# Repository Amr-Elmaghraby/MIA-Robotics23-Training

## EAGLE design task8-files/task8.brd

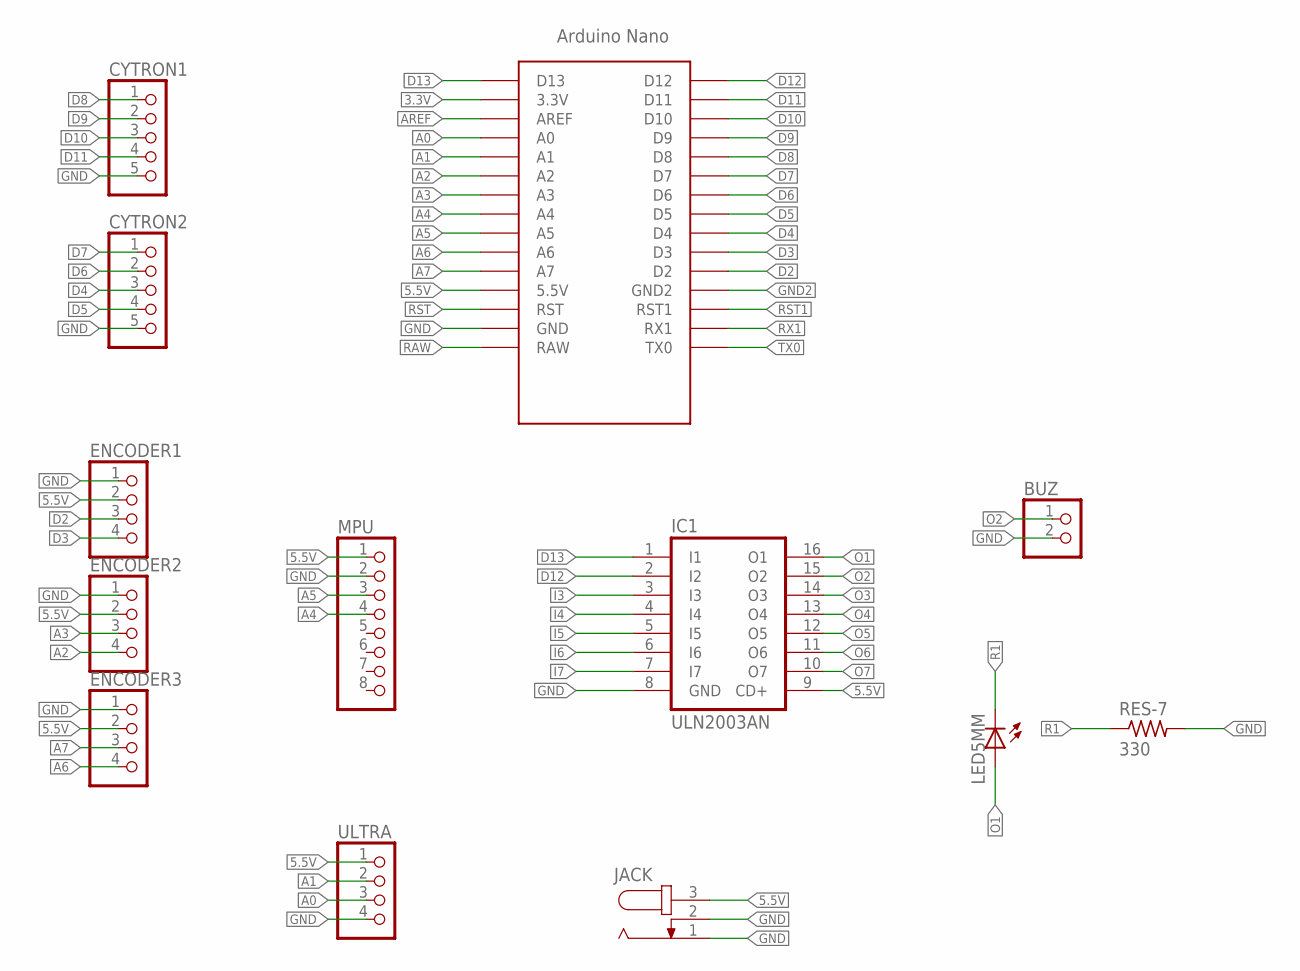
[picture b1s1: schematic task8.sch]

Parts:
330: RES-7; 0204/7
BUZ: PINHD-1X2; 1X02
CYTRON1, CYTRON2: PINHD-1X5; 1X05
ENCODER1, ENCODER2, ENCODER3: PINHD-1X4; 1X04
IC1: ULN2003AN; DIL16
JACK: JACK-PLUG0; SPC4077
MPU: PINHD-1X8; 1X08
U$1: ARDUINO_NANO; NANO
U$3: LED5MM
ULTRA: PINHD-1X4; 1X04

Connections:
3.3V: U$1.3.3V
5.5V: ENCODER1.2, ENCODER2.2, ENCODER3.2, IC1.9 (CD+), JACK.3, MPU.1, U$1.5V (5.5V), ULTRA.1
A0: U$1.A0, ULTRA.3
A1: U$1.A1, ULTRA.2
A2: ENCODER2.4, U$1.A2
A3: ENCODER2.3, U$1.A3
A4: MPU.4, U$1.A4
A5: MPU.3, U$1.A5
A6: ENCODER3.4, U$1.A6
A7: ENCODER3.3, U$1.A7
AREF: U$1.AREF
D2: ENCODER1.3, U$1.D2
D3: ENCODER1.4, U$1.D3
D4: CYTRON2.3, U$1.D4
D5: CYTRON2.4, U$1.D5
D6: CYTRON2.2, U$1.D6
D7: CYTRON2.1, U$1.D7
D8: CYTRON1.1, U$1.D8
D9: CYTRON1.2, U$1.D9
D10: CYTRON1.3, U$1.D10
D11: CYTRON1.4, U$1.D11
D12: IC1.2 (I2), U$1.D12
D13: IC1.1 (I1), U$1.D13
GND: 330.2, BUZ.2, CYTRON1.5, CYTRON2.5, ENCODER1.1, ENCODER2.1, ENCODER3.1, IC1.8 (GND), JACK.1, JACK.2, MPU.2, U$1.GND, ULTRA.4
GND2: U$1.GND1 (GND2)
I3: IC1.3 (I3)
I4: IC1.4 (I4)
I5: IC1.5 (I5)
I6: IC1.6 (I6)
I7: IC1.7 (I7)
O1: IC1.16 (O1), U$3.A
O2: BUZ.1, IC1.15 (O2)
O3: IC1.14 (O3)
O4: IC1.13 (O4)
O5: IC1.12 (O5)
O6: IC1.11 (O6)
O7: IC1.10 (O7)
R1: 330.1, U$3.K (C)
RAW: U$1.RAW
RST: U$1.RST
RST1: U$1.RST1
RX1: U$1.RX1
TX0: U$1.TX0

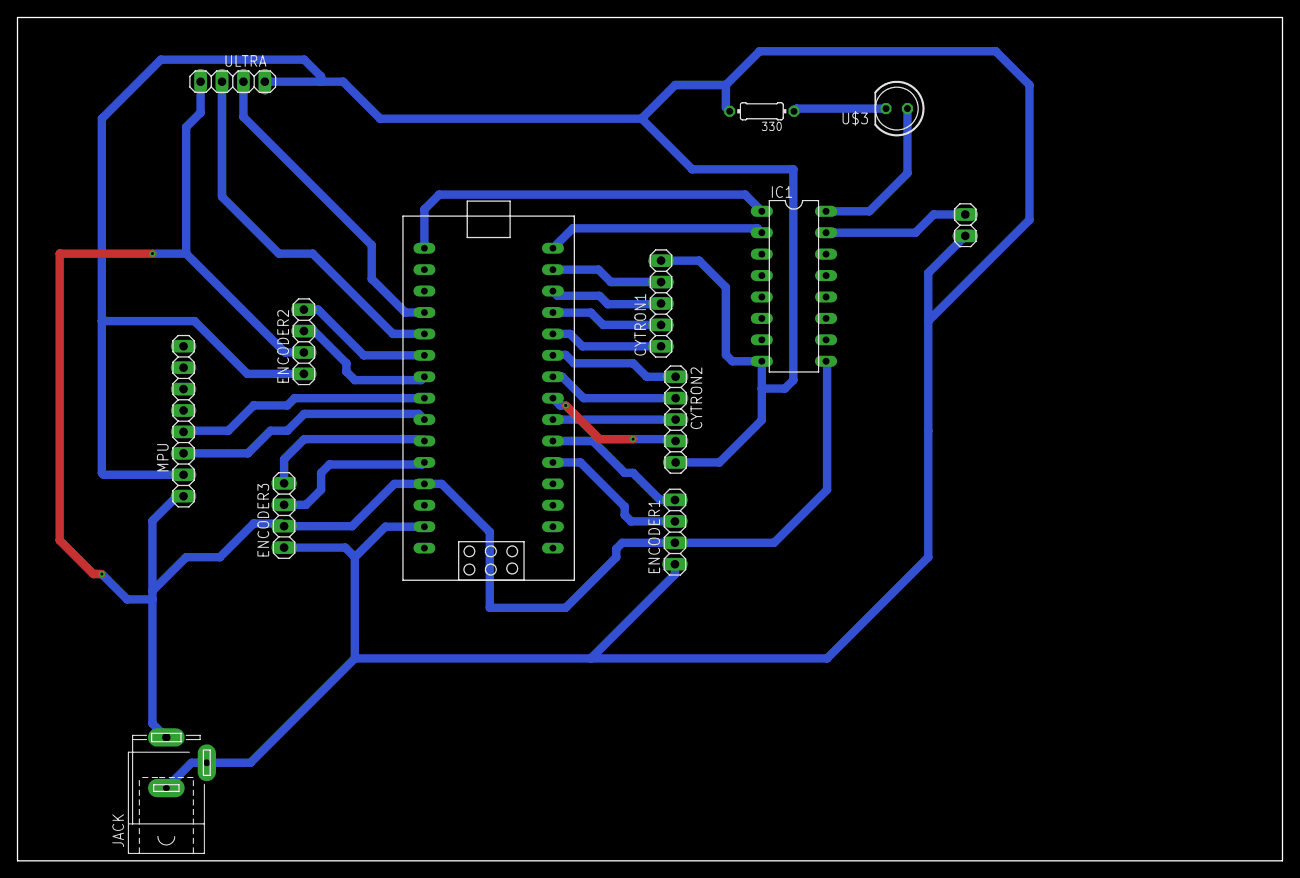
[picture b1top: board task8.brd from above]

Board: 2 copper layers, 150.0 x 100.0 mm, 13 parts (0 on the bottom side), 25 nets.

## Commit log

2022-08-23 01019721948_task1.zip removwd
2022-08-23 01019721948_task3.zip removed
2022-08-23 removed
2022-08-26 task2.ipynb
2022-08-26 task3
2022-08-29 aaaaa
2022-08-29 aaaaAA
2022-08-30 aaaa
2022-09-07 amrr
